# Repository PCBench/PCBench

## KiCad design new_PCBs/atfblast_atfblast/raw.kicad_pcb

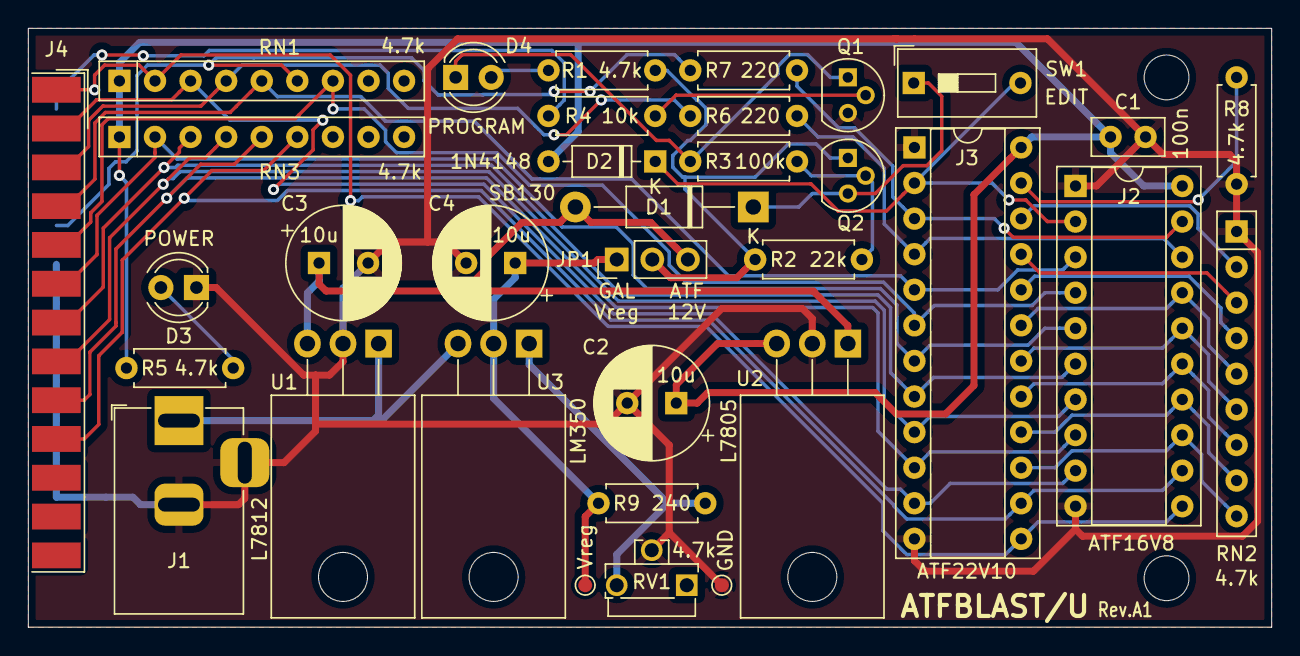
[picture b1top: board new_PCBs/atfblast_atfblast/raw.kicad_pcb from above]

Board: 2 copper layers, 88.8 x 42.8 mm, 36 parts (0 on the bottom side), 37 nets.

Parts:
C1: 100n; C_Disc_D5.0mm_W2.5mm_P2.50mm
C2, C3, C4: 10u; CP_Radial_D8.0mm_P3.50mm
D1: SB130; D_DO-41_SOD81_P12.70mm_Horizontal
D2: 1N4148; D_DO-35_SOD27_P7.62mm_Horizontal
D3, D4: LED; LED_D4.0mm
H1, H2: MountingHole; MountingHole_3.2mm_M3
J1: DS-210; BarrelJack_Horizontal
J2: DIP20-panel; DIP-20_W7.62mm_Socket
J3: DIP24-panel; DIP-24_W7.62mm_Socket
J4: DB25_Male; DSUB-25_Male_EdgeMount_P2.77mm
JP1: Jumper_3; PinHeader_1x03_P2.54mm_Vertical
Q1: BC547; TO-92
Q2: BC557; TO-92
R1, R5, R8: 4.7k; R_Axial_DIN0207_L6.3mm_D2.5mm_P7.62mm_Horizontal
R2: 22k; R_Axial_DIN0207_L6.3mm_D2.5mm_P7.62mm_Horizontal
R3: 100k; R_Axial_DIN0207_L6.3mm_D2.5mm_P7.62mm_Horizontal
R4: 10k; R_Axial_DIN0207_L6.3mm_D2.5mm_P7.62mm_Horizontal
R6, R7: 220; R_Axial_DIN0207_L6.3mm_D2.5mm_P7.62mm_Horizontal
R9: 240; R_Axial_DIN0207_L6.3mm_D2.5mm_P7.62mm_Horizontal
RN1, RN2, RN3: 4.7k; R_Array_SIP9
RV1: 4.7k; Potentiometer_Runtron_RM-063_Horizontal
SW1: SW_DIP_x01; SW_DIP_SPSTx01_Slide_9.78x4.72mm_W7.62mm_P2.54mm
TP1: Vreg; TestPoint_Pad_D1.0mm
TP2: GND; TestPoint_Pad_D1.0mm
U1: L7812; TO-220-3_Horizontal_TabDown
U2: L7805; TO-220-3_Horizontal_TabDown
U3: LM350; TO-220-3_Horizontal_TabDown

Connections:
+5V: C1.1, C2.1, D2.2 (A), J2.20, J3.24, R5.1, RN1.1 (common), RN3.1 (common), U2.3 (OUT)
+12V: C3.1, D1.2 (A), JP1.3 (B), U1.3 (OUT), U2.1 (IN)
/ACK: J2.12, J3.14, J4.10, RN3.6 (R5)
/AUTO: J4.14, R4.2
/D0: J2.9, J3.11, J4.2, RN1.3 (R2)
/D1: J4.3, R6.2, RN1.4 (R3)
/D2: J2.3, J3.5, J4.4, RN1.5 (R4)
/D3: J2.4, J3.6, J4.5, RN1.7 (R6)
/D4: J2.5, J3.7, J4.6, RN3.2 (R1)
/D5: J2.6, J3.8, J4.7, RN3.3 (R2)
/D6: J2.7, J3.9, J4.8, RN3.4 (R3)
/D7: J2.8, J3.10, J4.9, RN3.5 (R4)
/EDIT: D2.1 (K), J2.2, J3.2, SW1.2
/P_V-: J2.19, J3.3, R7.1
/RA0: J2.18, J3.4, R6.1
/SELECT: J4.17, R7.2, RN1.6 (R5)
/STROBE: J2.11, J3.13, J4.1, RN1.2 (R1)
GND: C1.2, C2.2, C3.2, C4.2, D3.1 (K), J1.2, J1.3, J2.1, J2.10, J3.1, J3.12, J4.18, J4.19, J4.20, J4.21, J4.22, J4.23, J4.24, Q1.3 (E), R8.2, RN2.1 (common), RV1.2, TP2.1, U1.2 (GND), U2.2 (GND)
unnamed: C4.1, JP1.1 (A), R9.1, TP1.1, U3.2 (VO)
unnamed: D1.1 (K), Q2.3 (C), SW1.1
unnamed: D3.2 (A), R5.2
unnamed: D4.1 (K), Q1.1 (C), R3.1
unnamed: D4.2 (A), R1.2
unnamed: J1.1, U1.1 (IN), U3.3 (VI)
unnamed: J2.13, J3.15, RN2.9 (R8)
unnamed: J2.14, J3.16, RN2.8 (R7)
unnamed: J2.15, J3.17, RN2.7 (R6)
unnamed: J2.16, J3.18, RN2.6 (R5)
unnamed: J2.17, J3.19, RN2.5 (R4)
unnamed: J3.20, RN2.4 (R3)
unnamed: J3.21, RN2.3 (R2)
unnamed: J3.22, RN2.2 (R1)
unnamed: J3.23, R8.1
unnamed: JP1.2 (C), Q2.1 (E), R1.1, R2.2
unnamed: Q1.2 (B), R4.1
unnamed: Q2.2 (B), R2.1, R3.2
unnamed: R9.2, RV1.3, U3.1 (ADJ)

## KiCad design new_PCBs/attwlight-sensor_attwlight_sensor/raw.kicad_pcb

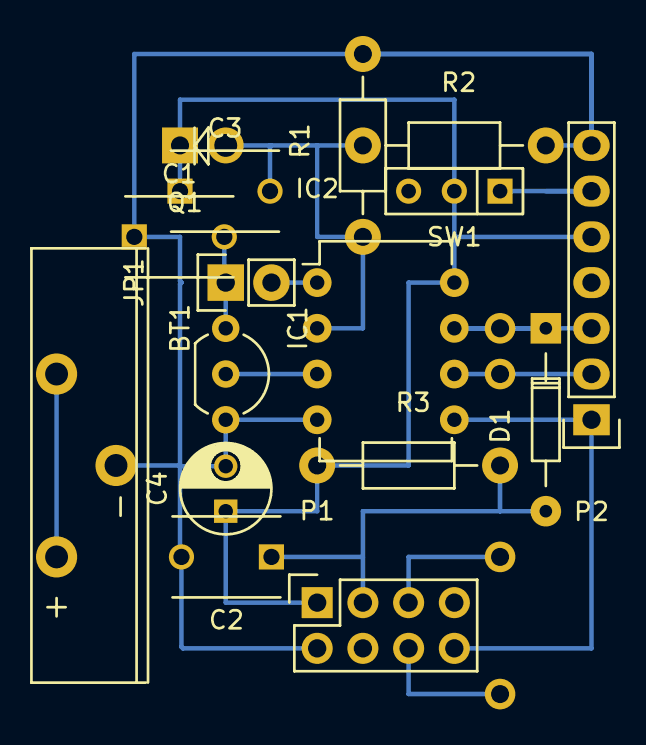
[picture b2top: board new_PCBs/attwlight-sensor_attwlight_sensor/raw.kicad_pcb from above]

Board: 2 copper layers, 16 parts (0 on the bottom side), 12 nets.

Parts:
BT1: 3V; CR2032V
C1, C3: 0.1μF; C_Disc_D6_P5
C2: 10nF; C_Disc_D6_P5
C4: 10μF; C_Radial_D5_L6_P2.5
D1: 1N4148; Diode_DO-35_SOD27_Horizontal_RM10
IC1: TMP36; TO-92_Inline_Wide
IC2: ATTINY85-P; DIP-8_W7.62mm
JP1: JUMPER; Pin_Header_Straight_1x02
P1: NRF24L01+; Socket_Strip_Straight_2x04
P2: PROGRAMMER; Pin_Header_Straight_1x07
Q1: BPW17N
R1: R; Resistor_Horizontal_RM10mm
R2: 10MΩ; Resistor_Horizontal_RM10mm
R3: 22kΩ; Resistor_Horizontal_RM10mm
SW1: Switch_SPDT; SW_Micro_SPST

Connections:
+BATT: BT1.1, SW1.3
CSN: C2.1, D1.2, P1.3, R3.2
Earth: BT1.2, C1.1, C2.2, C4.2, IC1.3, IC2.4, P1.2, P2.7, R1.2, R2.2
LS: C3.2, IC2.2, Q1.2, R1.1, R2.1
MISO: IC2.6, P1.5, P2.2
MOSI: IC2.5, P1.8, P2.1
unnamed: C1.2, IC1.1, JP1.1
unnamed: P2.6, SW1.1
RST: IC2.1, JP1.2, P2.4
SCK: D1.1, IC2.7, P1.6, P2.3
TMP: IC1.2, IC2.3
VCC: C3.1, C4.1, IC2.8, P1.1, P1.4, P2.5, Q1.1, R3.1, SW1.2

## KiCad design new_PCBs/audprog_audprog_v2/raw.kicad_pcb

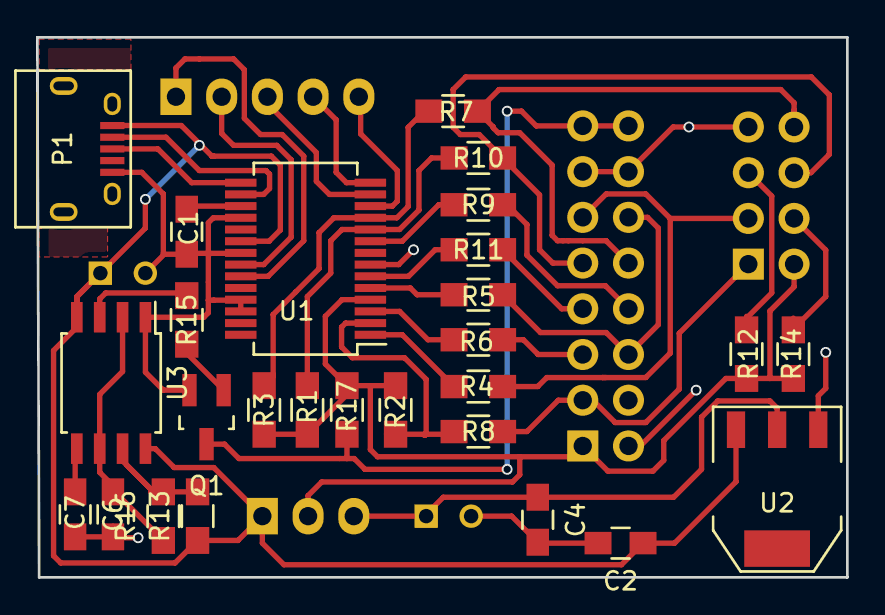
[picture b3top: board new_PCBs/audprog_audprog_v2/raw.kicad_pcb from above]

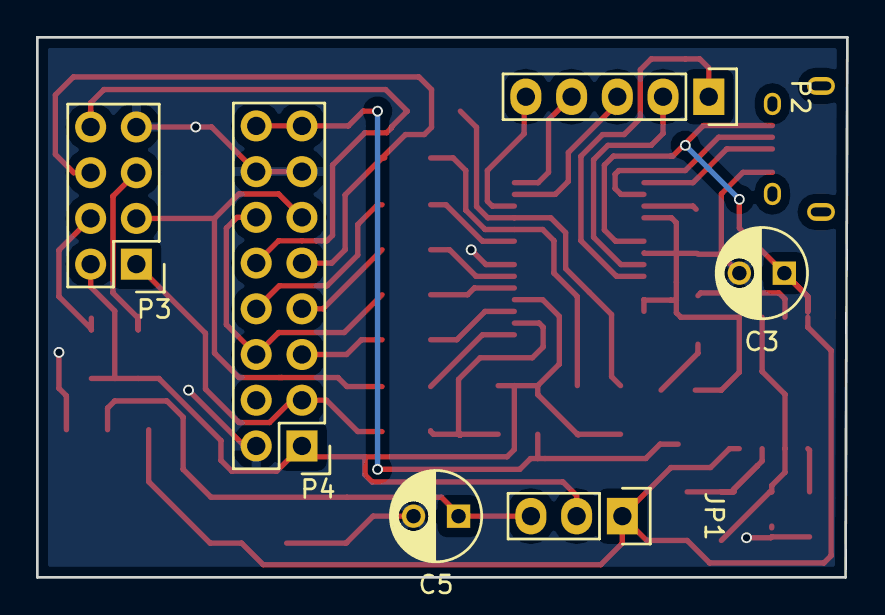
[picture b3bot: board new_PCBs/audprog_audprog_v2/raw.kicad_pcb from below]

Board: 2 copper layers, 45.0 x 30.0 mm, 33 parts (6 on the bottom side), 36 nets.

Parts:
C1, C6: 100n; C_0805_HandSoldering
C2, C4: 0,1u; C_0805_HandSoldering
C3, C5: 470u; C_Radial_D5_L11_P2.5
C7: 10n; C_0805_HandSoldering
JP1: Vcc_IO_SW; Pin_Header_Straight_1x03
P1: USB_OTG; USB_Micro-B
P2: CONN_01X05; Pin_Header_Straight_1x05
P3: CONN_02X04; Pin_Header_Straight_2x04
P4: CONN_02X08; Pin_Header_Straight_2x08
Q1: BC817; SOT-23_Handsoldering
R1, R2, R3: 5,6k; R_0805_HandSoldering
R4, R5, R6, R7, R8, R9, R10, R11: 22; R_0805_HandSoldering
R12, R14, R15, R17: 10k; R_0805_HandSoldering
R13: 1k; R_0805_HandSoldering
R16: 47,5k; R_0805_HandSoldering
U1: FT232RL; SSOP-28_5.3x10.2mm_Pitch0.65mm
U2: AP1117E33; SOT-223
U3: LM555N; SOIJ-8_5.3x5.3mm_Pitch1.27mm

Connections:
+3V3: C4.1, C5.1, JP1.3, U2.2
+5V: C2.1, C3.1, JP1.1, P1.1, R13.1, U1.20, U2.3, U3.4, U3.8
AUD_CK: P3.6, P4.9, R10.1
AUD_DATA0: P4.5, R6.1
AUD_DATA1: P4.6, P4.12, R5.1
AUD_DATA2: P4.7, R11.1
AUD_DATA3: P4.8, R9.1
AUD_RST: P3.1, P4.3, R8.1
AUD_SYNC: P3.8, P4.10, R7.1
BOOT_TX: P3.3, P4.11, R4.1
CBUS1: P2.1, U1.23
CBUS2: P2.2, U1.22
CBUS3: P2.3, U1.13
CBUS4: P2.4, U1.14
CBUS5: P2.5, U1.12
GND: C1.2, C2.2, C3.2, C4.2, C5.2, C6.2, C7.2, P1.5, P3.7, P4.2, P4.13, P4.14, Q1.2, U1.7, U1.18, U1.21, U1.25, U1.26, U2.1, U3.1
unnamed: C1.1, U1.17
unnamed: C6.1, R16.1, U3.2, U3.6
unnamed: C7.1, U3.5
unnamed: P1.2, U1.16
unnamed: P1.3, U1.15
unnamed: P3.4, R14.2
unnamed: P3.5, R12.1
unnamed: Q1.1, R15.1
unnamed: R1.2, R10.2, U1.10
unnamed: R2.2, R8.2, U1.2
unnamed: R3.2, R7.2, U1.11
unnamed: R4.2, U1.1
unnamed: R5.2, U1.5
unnamed: R6.2, U1.3
unnamed: R9.2, U1.9
unnamed: R11.2, U1.6
unnamed: R13.2, R16.2, U3.7
unnamed: R15.2, U3.3
VCC_IO: JP1.2, P3.2, P4.1, R1.1, R2.1, R3.1, R12.2, R14.1, R17.1, U1.4
WDT: P4.15, P4.16, Q1.3, R17.2

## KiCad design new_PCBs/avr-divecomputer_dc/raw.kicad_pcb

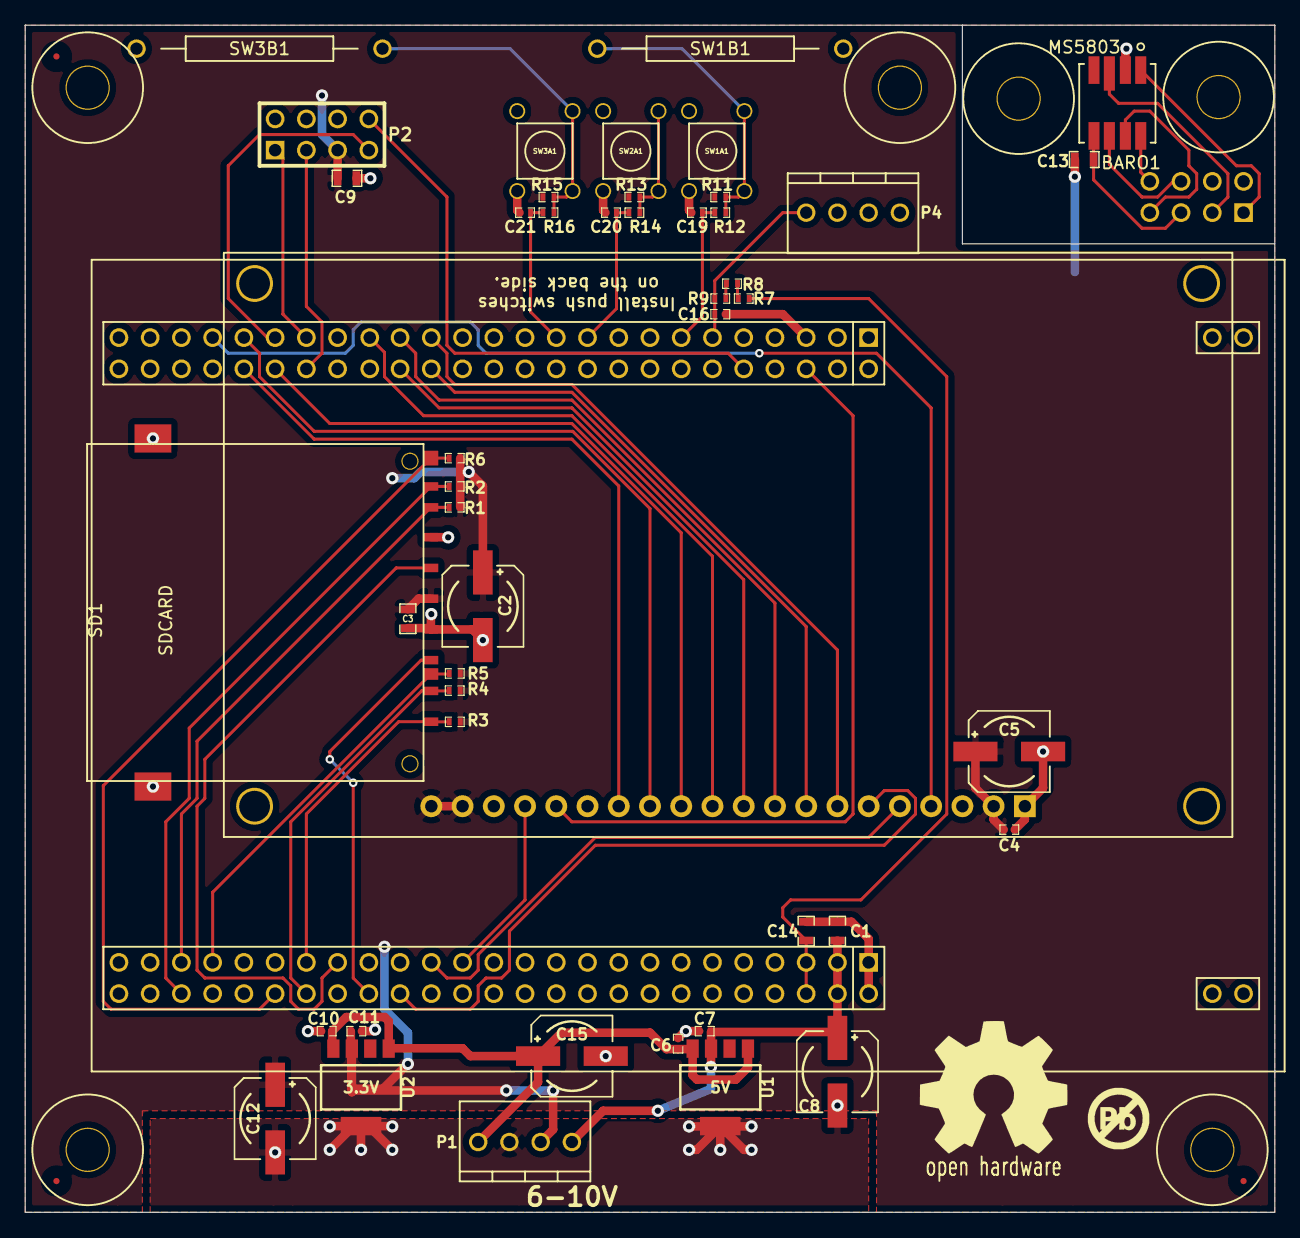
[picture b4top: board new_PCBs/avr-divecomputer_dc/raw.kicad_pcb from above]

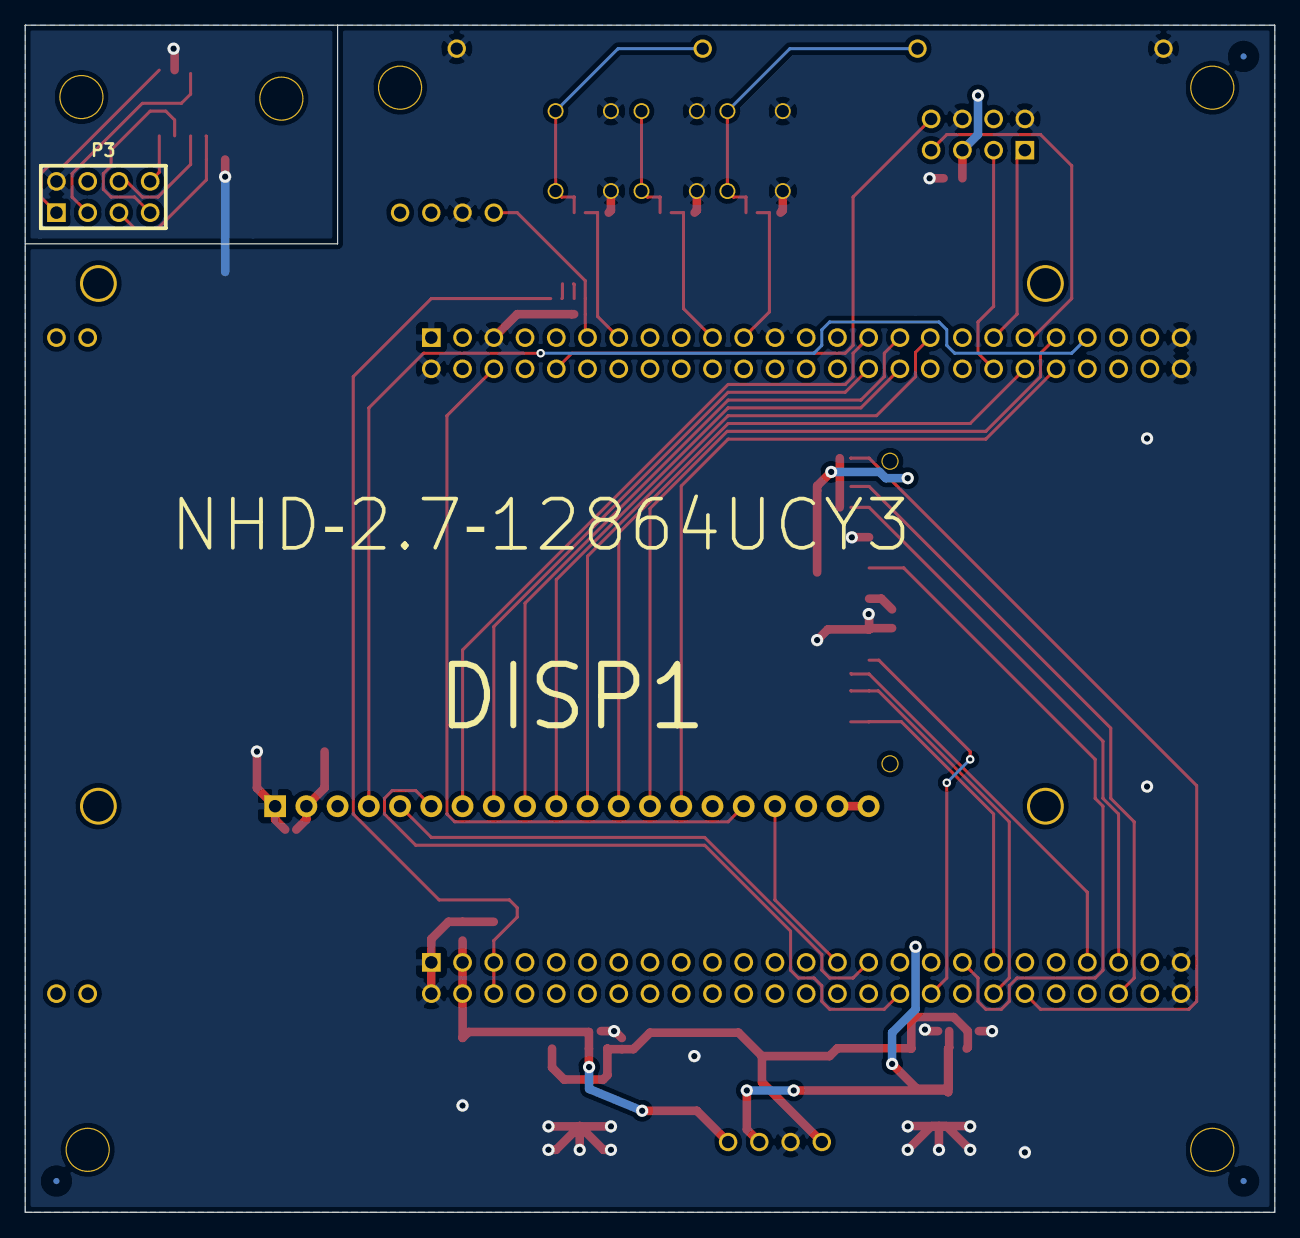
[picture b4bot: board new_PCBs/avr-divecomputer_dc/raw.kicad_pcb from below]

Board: 2 copper layers, 101.6 x 96.5 mm, 58 parts (2 on the bottom side), 45 nets.

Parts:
BARO1: MS5803
C1, C3, C9, C13, C14: 10uF; SM0603_Capa
C2, C5, C8, C12, C15: 150uF; c_elec_6.3x5.7
C4, C6, C7, C10, C11, C16, C19, C20, C21: 1uF; SM0402_c
DISP1: NHD‐2.7‐12864UCY3
FID1: FID**; FIDUCIAL
FID2, FID3: VAL**; FIDUCIAL
J1: STM32F4_DISCOVERY_HEADER; stm32f4_discovery_header
M3_MOUNT, M3_MOUNT#2, M3_MOUNT#3, M3_MOUNT#4, M3_MOUNT#5, M3_MOUNT#6: VAL**; M3_MOUNT
P1, P4: CONN_4; ED10563-ND
P2, P3: CONN_4X2; pin_array_4x2
R1, R2, R3, R4, R5, R6, R7, R8, R9, R11, R12, R13, R14, R15, R16: 100k; SM0402
SD1: SDCARD; 101-00405-75-ND
SW1A1, SW2A1, SW3A1: SW_PUSH; P8008S-ND
SW1B1, SW3B1: SW_PUSH; REED
U1: 5V; SOT-223-5
U2: 3.3V; SOT-223-5

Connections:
+3.3V: C2.1, C3.1, C4.1, C5.1, C9.1, C11.1, C12.1, DISP1.2, DISP1.19, DISP1.20, P1.3, P2.5, R1.1, R2.1, R3.1, R4.1, R5.2, R6.2, R11.2, R13.2, R15.2, SD1.4, U2.3
+5V: C1.1, C7.1, C8.1, J1.97, J1.98, P1.4, U1.3
+BATT: C6.1, C10.1, C15.1, P1.1, U1.1, U1.4, U2.1, U2.4
DEPTH_CS: J1.38, P2.3
FSMC_A16: DISP1.4, J1.43
FSMC_D08: DISP1.7, J1.29
FSMC_D09: DISP1.8, J1.30
FSMC_D10: DISP1.9, J1.31
FSMC_D11: DISP1.10, J1.32
FSMC_D12: DISP1.11, J1.33
FSMC_D13: DISP1.12, J1.40
FSMC_D14: DISP1.13, J1.41
FSMC_D15: DISP1.14, J1.42
FSMC_NE1: DISP1.17, J1.73
FSMC_NOE: DISP1.6, J1.70
FSMC_NWE: DISP1.5, J1.71
GND: BARO1.2, C1.2, C2.2, C3.2, C4.2, C5.2, C6.2, C7.2, C8.2, C9.2, C10.2, C11.2, C12.2, C13.2, C14.2, C15.2, C16.2, C19.2, C20.2, C21.2, DISP1.1, J1.1, J1.2, J1.5, J1.23, J1.49, J1.50, J1.51, J1.52, J1.99, J1.100, P1.2, P2.2, P2.6, P3.2, P4.3, SD1.3, SD1.6, SD1.10, SW1A1.1, SW1B1.1, SW2A1.1, SW3A1.1, SW3B1.1, U1.5, U2.5
unnamed: R11.1, R12.1, SW1A1.2, SW1B1.2
unnamed: R7.1, R8.2
unnamed: R8.1, R9.1
unnamed: R13.1, R14.1, SW2A1.2
unnamed: R15.1, R16.1, SW3A1.2, SW3B1.2
unnamed: BARO1.8, P3.8
unnamed: BARO1.7, P3.7
unnamed: BARO1.6, P3.6
unnamed: BARO1.5, C13.1, P3.5
unnamed: BARO1.1, P3.1
unnamed: BARO1.3, P3.3
RESET: DISP1.16, J1.6
SDIO_CK: J1.65, SD1.5
SDIO_CMD: J1.68, SD1.2
SDIO_D0: J1.55, R1.2, SD1.7
SDIO_D1: J1.56, R2.2, SD1.8
SDIO_D2: J1.63, R3.2, SD1.9
SDIO_D3: J1.64, R4.2, SD1.1
SD_CD: J1.57, R5.1, SD1.11
SD_WP: J1.62, R6.1, SD1.12
SPI2_MISO: J1.10, P2.8
SPI2_MOSI: J1.39, P2.7
SPI2_SCK: J1.37, P2.1
STM_3V: C14.1, J1.95, J1.96, R7.2
SW1: C19.1, J1.13, R12.2
SW2: C20.1, J1.19, R14.2
SW3: C21.1, J1.21, R16.2
WATER: C16.1, J1.11, P4.4, R9.2

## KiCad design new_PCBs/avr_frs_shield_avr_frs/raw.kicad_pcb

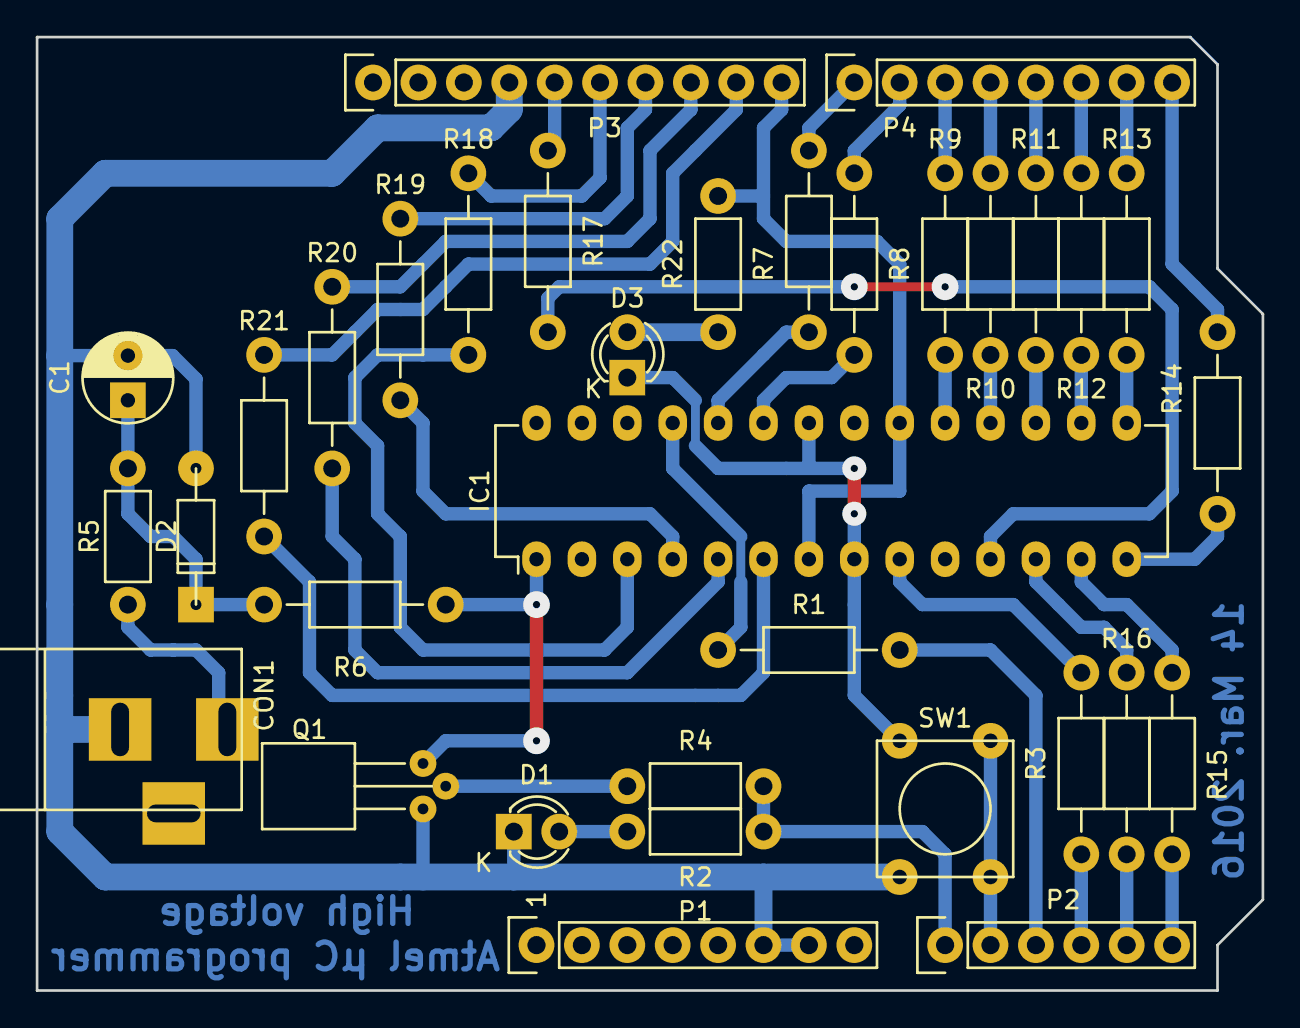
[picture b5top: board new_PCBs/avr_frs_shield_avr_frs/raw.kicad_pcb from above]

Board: 2 copper layers, 68.6 x 53.3 mm, 34 parts (0 on the bottom side), 44 nets.

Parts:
C1: 10uF; C_Radial_D5_L6_P2.5
CON1: BARREL_JACK
D1, D3: LED; LED-3MM
D2: 12V; DO-35
IC1: ATMEGA328P-P; DIP-28_W7.62mm
P1: Power; Socket_Strip_Arduino_1x08
P2: Analog; Socket_Strip_Arduino_1x06
P3: Digital; Socket_Strip_Arduino_1x10
P4: Digital; Socket_Strip_Arduino_1x08
Q1: Q_NPN_EBC; TO-92_Horizontal2_Molded_Narrow
R1, R3, R6, R7, R8, R9, R10, R11, R12, R13, R14, R15, R16, R17, R18, R19, R20, R21: 1K; Resistor_Horizontal_RM10mm
R2, R4: 1K; Resistor_Horizontal_RM7mm
R5: 100; Resistor_Horizontal_RM7mm
R22: 390; Resistor_Horizontal_RM7mm
SW1: SW_PUSH; SW_PUSH_SMALL

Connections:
/0(Rx): P4.8, R14.2
/1(Tx): P4.7, R13.2
/2: P4.6, R12.2
/3(**): P4.5, R11.2
/4: P4.4, R10.2
/5(**): P4.3, R9.2
/6(**): P4.2, R8.2
/7: P4.1, R7.2
/8: IC1.7, IC1.20, P3.10, R22.2
/9(**): P3.9, R21.2
/10(**/SS): P3.8, R20.2
/11(**/MOSI): P3.7, R19.2
/12(MISO): P3.6, R18.2
/13(SCK): P3.5, R17.2
/A0: P2.1, R2.1, R4.2
/A1: P2.2, SW1.2
/A2: P2.3, R1.2
/A3: P2.4, R3.2
/A4(SDA): P2.5, R16.2
/A5(SCL): P2.6, R15.2
GNDREF: C1.2, CON1.2, D1.1, D2.2, D3.1, IC1.8, IC1.22, P1.6, P1.7, P3.4, Q1.1, SW1.1
unnamed: C1.1, D2.1, R5.1, R6.2
unnamed: CON1.1, R5.2
unnamed: D1.2, R2.2
unnamed: D3.2, R22.1
unnamed: IC1.1, Q1.3, R6.1
unnamed: IC1.3, R18.1
unnamed: IC1.4, R19.1
unnamed: IC1.5, R20.1
unnamed: IC1.6, R21.1
unnamed: IC1.9, R3.1
unnamed: IC1.11, R17.1
unnamed: IC1.12, R16.1
unnamed: IC1.13, R15.1
unnamed: IC1.14, R14.1
unnamed: IC1.15, R13.1
unnamed: IC1.16, R12.1
unnamed: IC1.17, R11.1
unnamed: IC1.18, R10.1
unnamed: IC1.19, R9.1
unnamed: IC1.23, R8.1
unnamed: IC1.24, R7.1
unnamed: IC1.25, R1.1
unnamed: Q1.2, R4.1

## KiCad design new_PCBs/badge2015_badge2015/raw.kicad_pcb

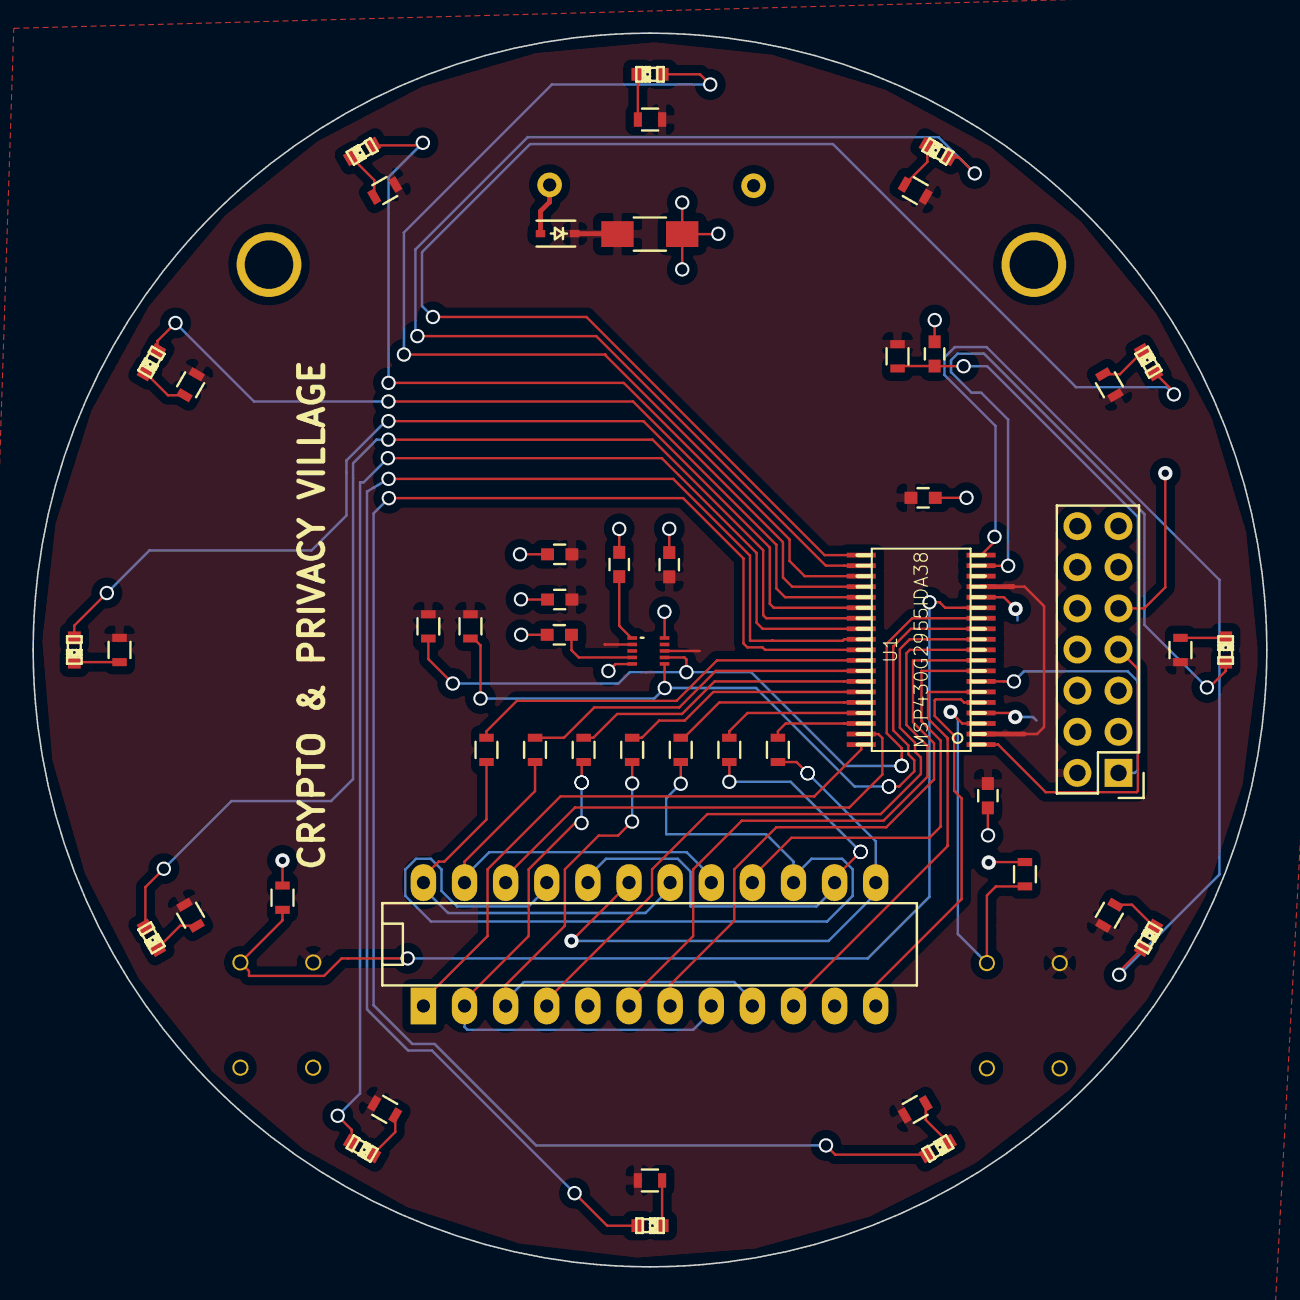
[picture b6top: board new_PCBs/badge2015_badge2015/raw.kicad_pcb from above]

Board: 2 copper layers, 76.2 x 76.2 mm, 55 parts (1 on the bottom side), 58 nets.

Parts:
2.2nF1: C; C_0603
BT1: Battery
C1, C2: 0.1uf; C_0603
C6: 47uF; C_1206_HandSoldering
C7: 1uf; C_0603
C8, C9, C10, C11: 100nf; C_0603
D1, D2, D3, D4, D5, D6, D7, D8, D9, D10, D11, D12: LED; LED-0603
D55: DIODE; SOD-323
MAG: MAG3110_10VFDFN
P1: CONN_01X14; Pin_Header_Straight_2x07
R1, R2, R3, R4, R5, R6, R7, R8, R9, R10, R11, R12: 499; R_0603
R13, R23: R; R_0603
R14, R15, R16, R17, R18, R21, R22: 680; R_0603
R19, R20: 4.7k; R_0603
R24: 47k; R_0603
SW1, SW2: SW_PUSH; push_btn
U1: MSP430G2955IDA38; AB2_TSSOP38_W
U4: 7SEGMENT; DIP-24__300_ELL
hole_l: hole
hole_r: hole_r; hole

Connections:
/3.3V: C1.1, C2.1, C6.1, C7.1, C8.1, C11.1, D55.2, MAG.2, MAG.8, P1.2, R1.1, R2.1, R3.1, R4.1, R5.1, R6.1, R7.1, R8.1, R9.1, R10.1, R11.1, R12.1, R19.1, R20.1, R24.1, SW1.1, SW2.1, U1.2, U1.16
/ANODE_a: R14.2, U4.12, U4.24
/ANODE_b: R15.2, U4.11, U4.23
/ANODE_c: R17.2, U4.3, U4.15
/ANODE_d: R21.2, U4.8, U4.20
/ANODE_dp: U4.5, U4.17
/ANODE_e: R16.2, U4.2, U4.14
/ANODE_f: R18.2, U4.9, U4.21
/ANODE_g: R22.2, U4.7, U4.19
/BAT+: BT1.1, D55.1
/CATHODE_1: U1.38, U4.1
/CATHODE_2: U1.37, U4.10
/CATHODE_3: U1.11, U4.4
/CATHODE_4: U1.10, U4.6
/CATHODE_5: U1.9, U4.13
/CATHODE_6: U1.8, U4.22
/CATHODE_7: U1.6, U4.16
/CATHODE_8: U1.5, U4.18
/P1(0): R15.1, U1.31
/P1(1): R16.1, U1.32
/P1(2): R17.1, U1.33
/P1(3): R18.1, U1.34
/P1(4): R21.1, U1.35
/P1(5): R22.1, U1.36
/P2(3): D2.2, U1.29
/P2(4): R14.1, U1.30
/P2(5): R13.1, SW1.2, U1.3
/P3(3): R23.1, SW2.2, U1.14
/P3(4): D10.2, U1.25
/P3(5): D11.2, U1.26
/P3(6): D12.2, U1.27
/P3(7): D1.2, U1.28
/P4(1): D4.2, U1.18
/P4(2): D3.2, U1.19
/P4(3): D5.2, U1.20
/P4(4): D6.2, U1.21
/P4(5): D7.2, U1.22
/P4(6): D8.2, U1.23
/P4(7): D9.2, U1.24
/SBWTCK: P1.7, U1.1
/SCL: MAG.7, R20.2, U1.13
/SDA: MAG.6, R19.2, U1.12
/~RST: 2.2nF1.1, P1.1, R24.2, U1.7
GND: 2.2nF1.2, BT1.2, C1.2, C2.2, C6.2, C7.2, C8.2, C9.1, C10.2, C11.2, MAG.5, MAG.10, P1.9, R13.2, R23.2, U1.4, U1.15
unnamed: C9.2, MAG.1
unnamed: C10.1, MAG.4
unnamed: D1.1, R1.2
unnamed: D2.1, R2.2
unnamed: D3.1, R3.2
unnamed: D4.1, R4.2
unnamed: D5.1, R5.2
unnamed: D6.1, R6.2
unnamed: D7.1, R7.2
unnamed: D8.1, R8.2
unnamed: D9.1, R9.2
unnamed: D10.1, R10.2
unnamed: D11.1, R11.2
unnamed: D12.1, R12.2

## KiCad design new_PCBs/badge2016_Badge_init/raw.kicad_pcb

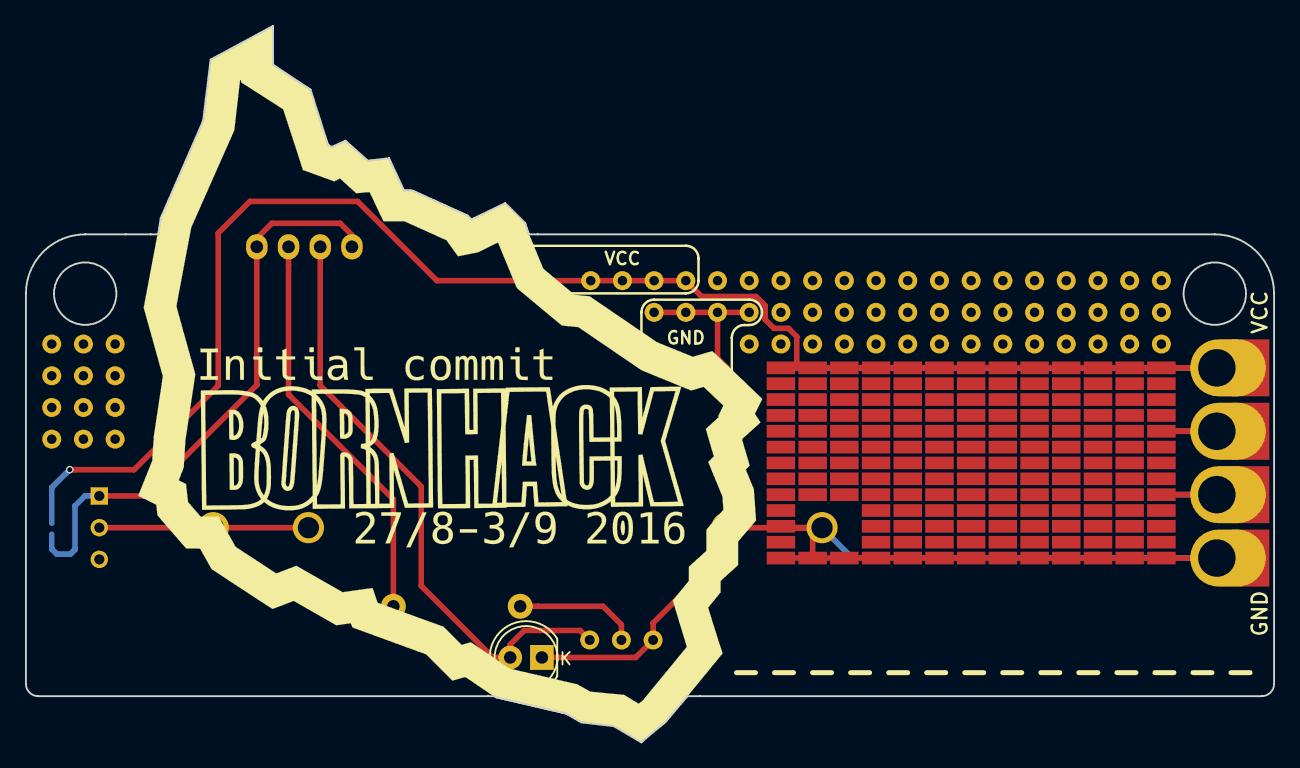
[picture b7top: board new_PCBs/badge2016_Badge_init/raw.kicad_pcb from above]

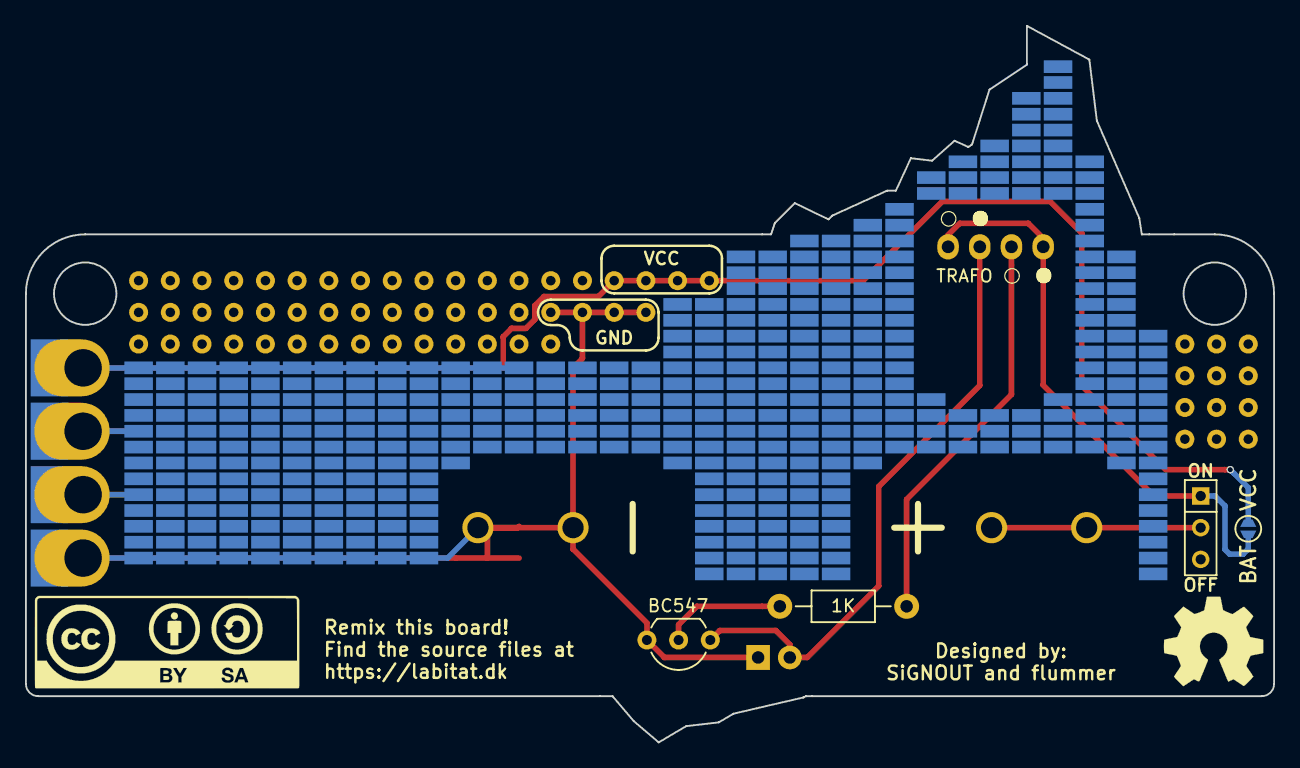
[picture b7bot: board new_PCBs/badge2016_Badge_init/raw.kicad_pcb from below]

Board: 2 copper layers, 100.0 x 57.4 mm, 9 parts (6 on the bottom side), 6 nets.

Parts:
BT1: Battery; BK-92
D1: LED; LED-5MM
JP1: Jumper_NC_Small; Solder_Jumper
P1, P2: CONN_01X01; PTH_Edge_Proto_Connector
Q1: BC547; TO-92_Inline_Wide
R1: 1K; Resistor_Horizontal_RM10mm
SW1: POWER; SW_Micro_SPST
T1: TRAFO; Pin_Header_Straight_1x04

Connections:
+BATT: JP1.1, SW1.1, T1.1, T1.4
GND: BT1.2, D1.1, Q1.3
unnamed: BT1.1, SW1.2
unnamed: D1.2, Q1.1, T1.3
unnamed: Q1.2, R1.2
unnamed: R1.1, T1.2
